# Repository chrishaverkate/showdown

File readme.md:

# Overview
A modern remake of my senior project from college. 

"Smoke & Hope" was my college project and was a competition shooting timer. It originally used:
* FPGA development board
  * I designed a soft-core processor and a custom DSP module in VHDL
  * Wrote the timing and graphics in C++
* Custom vibration sensor (for detecting the gun shot)
* Resistive touch screen

This project (also named after a classic competition shooting course) is a "re-take". I'm looking to:
* Modernize
* Miniaturize
* Make portable

## Features
* Built on the Raspberry Pi Pico
* 1.14 inch LCD display
* Custom PCB for the vibration sensor circuit
* Battery powered
* 3D printed case

## Resources
* [Raspberry Pi Pico](https://www.raspberrypi.org/products/raspberry-pi-pico/)
* [1.14 inch LCD display](https://www.pishop.us/product/1-14inch-lcd-display-module-for-raspberry-pi-pico-65k-colors-240-135-spi/)
* [Battery](https://www.pishop.us/product/lithium-ion-polymer-battery-3-7v-900mah/)

### Prerequisites
* [Docker](https://docs.docker.com/get-docker/)
* [Pico Probe](https://www.raspberrypi.org/documentation/rp2040/getting-started/#debug-probe)
* [Raspberry Pi Pico](https://www.raspberrypi.org/products/raspberry-pi-pico/)
* [CMake](https://cmake.org/download/)
* Compiler tools for your platform

### Build - Local
To build locally, use the convenience script [run-build-linux.bash](scripts/run-build-linux.bash).
You can see the details of the build for setting up an IDE for more interactive development.
```bash
cd scripts && ./run-build-linux.bash linux
```

### Build - Docker
Again, there is a convenience script [run-build-docker.bash](scripts/run-build-docker.bash).
```bash
cd scripts && ./run-build-docker.bash
```

The benefit to this script is the output will be placed in the 'bin' folder,
and it will be ready to flash to the Pico.

## LCD Display
Using the [Waveshare Pico LCD 1.14](https://www.waveshare.com/wiki/Pico-LCD-1.14) (2 buttons + dpad style).

**Front View**

**Pinout**

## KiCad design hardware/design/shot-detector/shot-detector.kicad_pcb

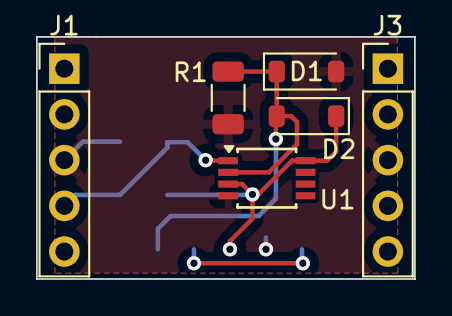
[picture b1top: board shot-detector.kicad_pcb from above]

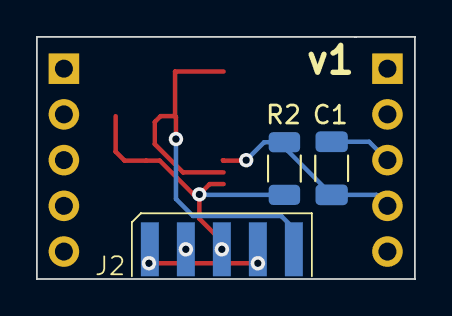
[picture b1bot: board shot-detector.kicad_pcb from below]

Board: 2 copper layers, 21.0 x 13.5 mm, 9 parts (3 on the bottom side), 5 nets.

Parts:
C1: C; C_1206_3216Metric
D1, D2: 1N4148; D_SOD-123
J1, J3: Conn_01x05; PinHeader_1x05_P2.54mm_Vertical
J2: Conn_01x05; 1x05_smt_wire_solder
R1: 1M; R_1206_3216Metric
R2: 10k; R_1206_3216Metric
U1: LM393; TSSOP-8_3x3mm_P0.65mm

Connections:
+5V: D2.1 (K), J2.3, R2.1, U1.3 (+_in1), U1.8 (V+)
/output: C1.1, J1.4, R2.2, U1.1
/pizo_conditioned: D1.1 (K), D2.2 (A), J2.5, R1.1, U1.2 (-_in1)
/pizo_in: J2.1, J2.4
GND: C1.2, D1.2 (A), J1.3, J2.2, J3.3, R1.2, U1.4 (V-)

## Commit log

2023-04-28 Initial setup of the project.
    It builds and runs some UI from my pico-eye project, but is enough to prove the wiring on my dev board.
2023-04-29 adding submodule refs
2023-04-29 Tinkering with screen settings.
    Mostly just getting the screen working and testing button input.
2023-04-30 Proof of Concept for one screen with scrolling.
    I tried drawing out a potential (novel) visualization of a shot timeline. The screen includes scrolling, so that many shots could be displayed.
    Also includes initial attempts at setting up a buzzer (not working yet).
2023-04-30 Basic buzzer operation.
    Just proving out a possible buzzer configuration.
2023-05-06 Adding UI and UX diagram.
2023-05-06 Adding initial class diagram and some class structures.
2023-05-07 Controller tests are started.
    This prompted some designing of the class structure and starting to fill in some of the skeleton of the project.
    Internal mechanics of Controller can track a list of views and switch the active view based on button presses.
2023-05-09 Views and switching views works!!
    There is a lot here, but the gist is that a pico specific screen that meets the showdown interface can be created and passed into a number of views on the showdown controller.
    Very basic button presses are captured and sent to the controller, which will change which view is being drawn.
2023-05-11 Getting the Session class connected to the Timeline view.
    Includes some hardcoded data in main for consistent testing while getting the session model correctly working. The Timeline view is also getting a first pass implementation. It's starting to come ali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
2023-05-11 Drawing improvement.
    Change drawing so that it happens in response to the controller processing user input. This makes the UX much more responsive because the screen isn't getting redrawn constantly!
2023-05-11 Time Table and Delta Time views are implemented.
    This gets the 3 primary review screens done for a first pass.
2023-05-13 Getting test build to work on Mac.
    Mostly just moving uint to uint8_t and adding a couple cmake files.
2023-05-31 Optimizing drawing so old shots are not re-drawn.
    Drawing on the 3 data screens is a lot faster for each consecutive shot. Also, connected the 'A' button to shot_detected for now.
2023-06-18 Setting up shot detection interrupt.
2023-06-18 Fixed shot delta table UI.
2023-07-01 Hacking in a way to scale an existing font.
    I needed something much larger than the basic demo fonts and creating a new table was out of the question.
2023-07-02 Finished first pass at home screen.
    The time of the last show and the number of total shots are displayed in very large font for easier reading!
2023-07-04 Buzzer now works properly.
    The buzzer starts when a new session is started and lasts for a configured time. Shots can be detected even while the buzzer is still sounding.
    Also, includes some refactoring to the button functions. Combining lambdas and templates to share as much code as possible.
2023-07-05 Starting the hardware design for shot detector circuit
2023-07-29 Starting to design hardware stack-up and introducing system info view.
    The goal of system info is to display battery information.
2023-08-12 Introducing System Info screen.
    The system will now determine if it is running on battery power or plugged in charging. The full system is operational either way, and the details of the battery is displayed on a system info screen.
    There is still work needed to get the screen to know when to update based on changes to system info.
2023-08-12 Added a way for a view to get a callback when the model is updated, skipping the controller.
    The good: now the system info is updated any time the system changes state and can directly invoke the correct view. This keeps the controller from needing to know anything special about the views it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
    The bad: seems a little complicated... also, the views now need to know if they are "active". Similar to an app or window knowing it's in the foreground or open.
2023-09-24 Working on the physical stackup.
    Updating diagram to show connection between Pico and other devices. Moving shot detection pin to be accessible by shot detection PCB.
2023-09-24 Adding Pico Lipo Shim documentation.
2025-11-15 Fixing up some cruft while getting back into the project.
2025-12-22 Updating schematic to use the LM393 along with some related docs
2026-03-15 Progress on schematic and PCB.
    Finished getting all the parts placed, and most all footprints.
    Getting the general layout started on PCB.
2026-03-16 First pass of PCB layout.
2026-03-23 V1 of PCB ordered.
